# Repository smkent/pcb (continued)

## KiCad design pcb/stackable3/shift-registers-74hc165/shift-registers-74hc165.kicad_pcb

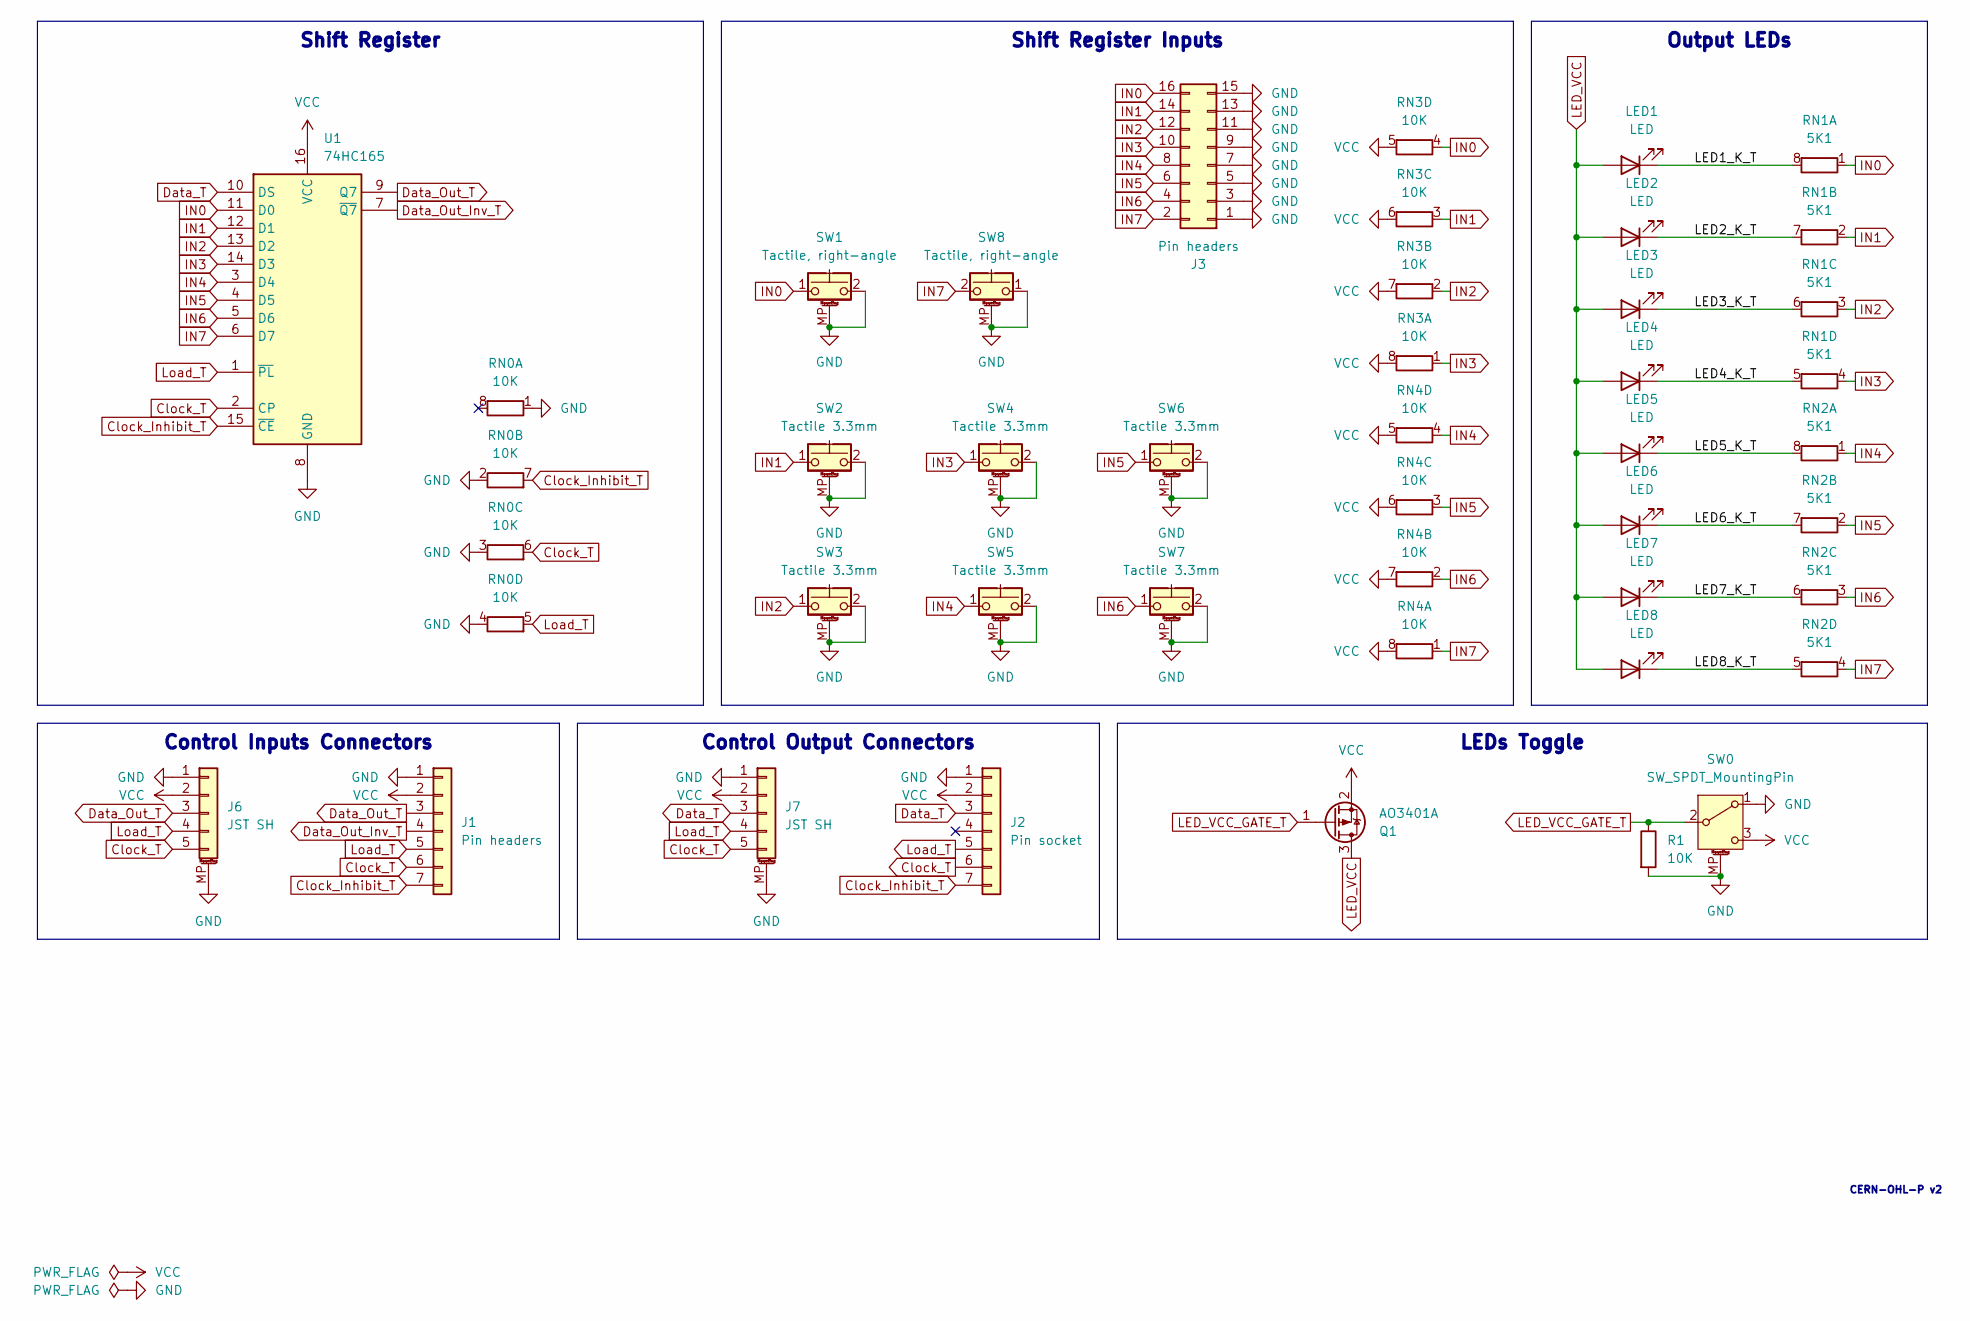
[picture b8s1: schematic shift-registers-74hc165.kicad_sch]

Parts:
J1: Pin headers; PinHeader_1x07_P2.54mm_Horizontal
J2: Pin socket; PinSocket_1x07_P2.54mm_Horizontal
J3: Pin headers; PinHeader_2x08_P2.54mm_Vertical
J6, J7: JST SH; JST_SH_SM05B-SRSS-TB_1x05-1MP_P1.00mm_Horizontal; LCSC Part C7433426
LED1, LED2, LED3, LED4, LED5, LED6, LED7, LED8: LED; LED_0402_1005Metric
Q1: AO3401A; SOT-23
R1: 10K; R_0402_1005Metric
RN0: 10K; R_Array_Convex_4x0603_HandSolder; LCSC Part C110924
RN1, RN2: 5K1; R_Array_Convex_4x0402; LCSC Part C425290
RN3, RN4: 10K; R_Array_Convex_4x0402; LCSC Part C7422173
SW0: SW_SPDT_MountingPin; SW_SPDT_PCM12; LCSC Part C319020
SW1, SW8: Tactile, right-angle; SW_Push_1P1T-MP_NO_4.6x3mm_Horizontal; LCSC Part C2888932
SW2, SW3, SW4, SW5, SW6, SW7: Tactile 3.3mm; SW_Push_1P1T_NO_3.3x3.3mm_MP
U1: 74HC165; SO-16_3.9x9.9mm_P1.27mm

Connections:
/LED1_K_T: LED1.1 (K), RN1.8 (R1.2)
/LED2_K_T: LED2.1 (K), RN1.7 (R2.2)
/LED3_K_T: LED3.1 (K), RN1.6 (R3.2)
/LED4_K_T: LED4.1 (K), RN1.5 (R4.2)
/LED5_K_T: LED5.1 (K), RN2.8 (R1.2)
/LED6_K_T: LED6.1 (K), RN2.7 (R2.2)
/LED7_K_T: LED7.1 (K), RN2.6 (R3.2)
/LED8_K_T: LED8.1 (K), RN2.5 (R4.2)
Clock_Inhibit_T: J1.7, J2.7, RN0.7 (R2.2), U1.15 (~CE)
Clock_T: J1.6, J2.6, J6.5, J7.5, RN0.6 (R3.2), U1.2 (CP)
Data_Out_Inv_T: J1.4, U1.7 (~Q7)
Data_Out_T: J1.3, J6.3, U1.9 (Q7)
Data_T: J2.3, J7.3, U1.10 (DS)
GND: J1.1, J2.1, J3.1, J3.3, J3.5, J3.7, J3.9, J3.11, J3.13, J3.15, J6.1, J6.MP (MountPin), J7.1, J7.MP (MountPin), R1.2, RN0.1 (R1.1), RN0.2 (R2.1), RN0.3 (R3.1), RN0.4 (R4.1), SW0.1 (A), SW0.MP (MountPin), SW1.2, SW1.MP (MountPin), SW2.2, SW2.MP (MountPin), SW3.2, SW3.MP (MountPin), SW4.2, SW4.MP (MountPin), SW5.2, SW5.MP (MountPin), SW6.2, SW6.MP (MountPin), SW7.2, SW7.MP (MountPin), SW8.1, SW8.MP (MountPin), U1.8 (GND)
IN0: J3.16, RN1.1 (R1.1), RN3.4 (R4.1), SW1.1, U1.11 (D0)
IN1: J3.14, RN1.2 (R2.1), RN3.3 (R3.1), SW2.1, U1.12 (D1)
IN2: J3.12, RN1.3 (R3.1), RN3.2 (R2.1), SW3.1, U1.13 (D2)
IN3: J3.10, RN1.4 (R4.1), RN3.1 (R1.1), SW4.1, U1.14 (D3)
IN4: J3.8, RN2.1 (R1.1), RN4.4 (R4.1), SW5.1, U1.3 (D4)
IN5: J3.6, RN2.2 (R2.1), RN4.3 (R3.1), SW6.1, U1.4 (D5)
IN6: J3.4, RN2.3 (R3.1), RN4.2 (R2.1), SW7.1, U1.5 (D6)
IN7: J3.2, RN2.4 (R4.1), RN4.1 (R1.1), SW8.2, U1.6 (D7)
LED_VCC: LED1.2 (A), LED2.2 (A), LED3.2 (A), LED4.2 (A), LED5.2 (A), LED6.2 (A), LED7.2 (A), LED8.2 (A), Q1.3 (D)
LED_VCC_GATE_T: Q1.1 (G), R1.1, SW0.2 (B)
Load_T: J1.5, J2.5, J6.4, J7.4, RN0.5 (R4.2), U1.1 (~PL)
VCC: J1.2, J2.2, J6.2, J7.2, Q1.2 (S), RN3.5 (R4.2), RN3.6 (R3.2), RN3.7 (R2.2), RN3.8 (R1.2), RN4.5 (R4.2), RN4.6 (R3.2), RN4.7 (R2.2), RN4.8 (R1.2), SW0.3 (C), U1.16 (VCC)

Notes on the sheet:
Control Inputs Connectors
Control Output Connectors
Output LEDs
Shift Register
Shift Register Inputs
LEDs Toggle
CERN-OHL-P v2

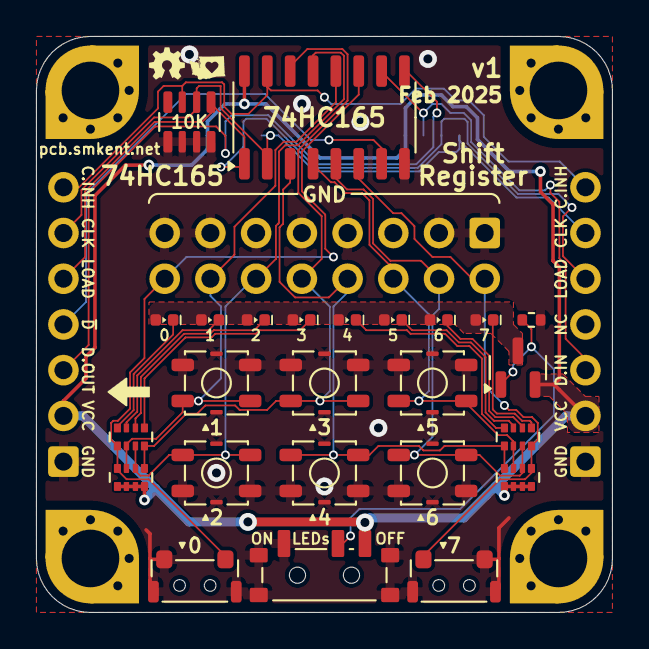
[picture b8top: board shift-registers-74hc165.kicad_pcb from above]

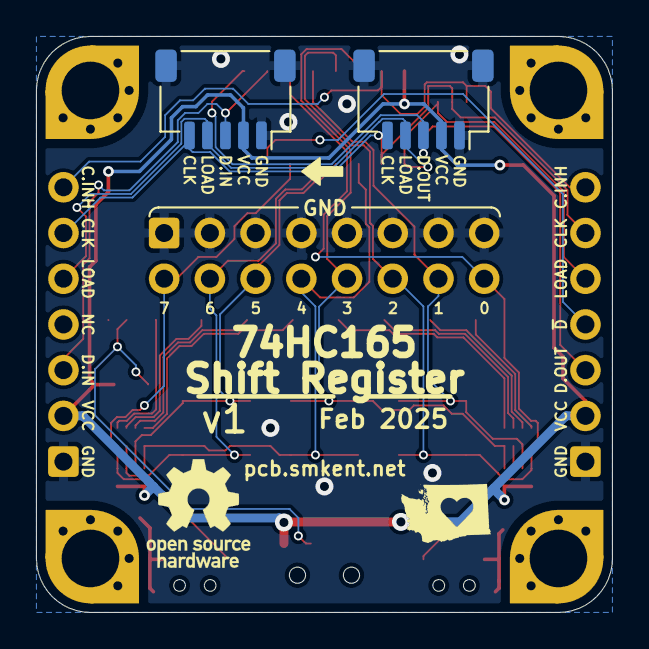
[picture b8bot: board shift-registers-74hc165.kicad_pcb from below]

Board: 2 copper layers, 32.0 x 32.0 mm, 30 parts (2 on the bottom side), 26 nets.

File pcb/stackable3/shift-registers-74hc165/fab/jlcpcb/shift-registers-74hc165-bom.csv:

Comment,Designator,Footprint,LCSC
Tactile 3.3mm,"SW2,SW3,SW4,SW5,SW6,SW7",electromechanical:SW_Push_1P1T_NO_3.3x3.3mm_MP,
LED,"LED1,LED2,LED3,LED4,LED5,LED6,LED7,LED8",discrete:LED_0402_1005Metric,
AO3401A,Q1,Package_TO_SOT_SMD:SOT-23,
74HC165,U1,Package_SO:SO-16_3.9x9.9mm_P1.27mm,
JST SH,"J6,J7",connector:JST_SH_SM05B-SRSS-TB_1x05-1MP_P1.00mm_Horizontal,C7433426
10K,"RN3,RN4",discrete:R_Array_Convex_4x0402,C7422173
"Tactile, right-angle","SW1,SW8",electromechanical:SW_Push_1P1T-MP_NO_4.6x3mm_Horizontal,C2888932
10K,RN0,discrete:R_Array_Convex_4x0603_HandSolder,C110924
SW_SPDT_MountingPin,SW0,electromechanical:SW_SPDT_PCM12,C319020
10K,R1,Resistor_SMD:R_0402_1005Metric,
Pin headers,J1,connector:PinHeader_1x07_P2.54mm_Horizontal,
5K1,"RN1,RN2",discrete:R_Array_Convex_4x0402,C425290
Pin socket,J2,connector:PinSocket_1x07_P2.54mm_Horizontal,
Pin headers,J3,connector:PinHeader_2x08_P2.54mm_Vertical,
